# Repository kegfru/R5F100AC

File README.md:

# R5F100AC
Renesas R5F100AC projects

ds18b20 - read from one 1-wire DS18B20 sensor and display temperature on SHD0028 7-segment display (http://www.smartmodule.ru/0028.html, based on SD16739STR)

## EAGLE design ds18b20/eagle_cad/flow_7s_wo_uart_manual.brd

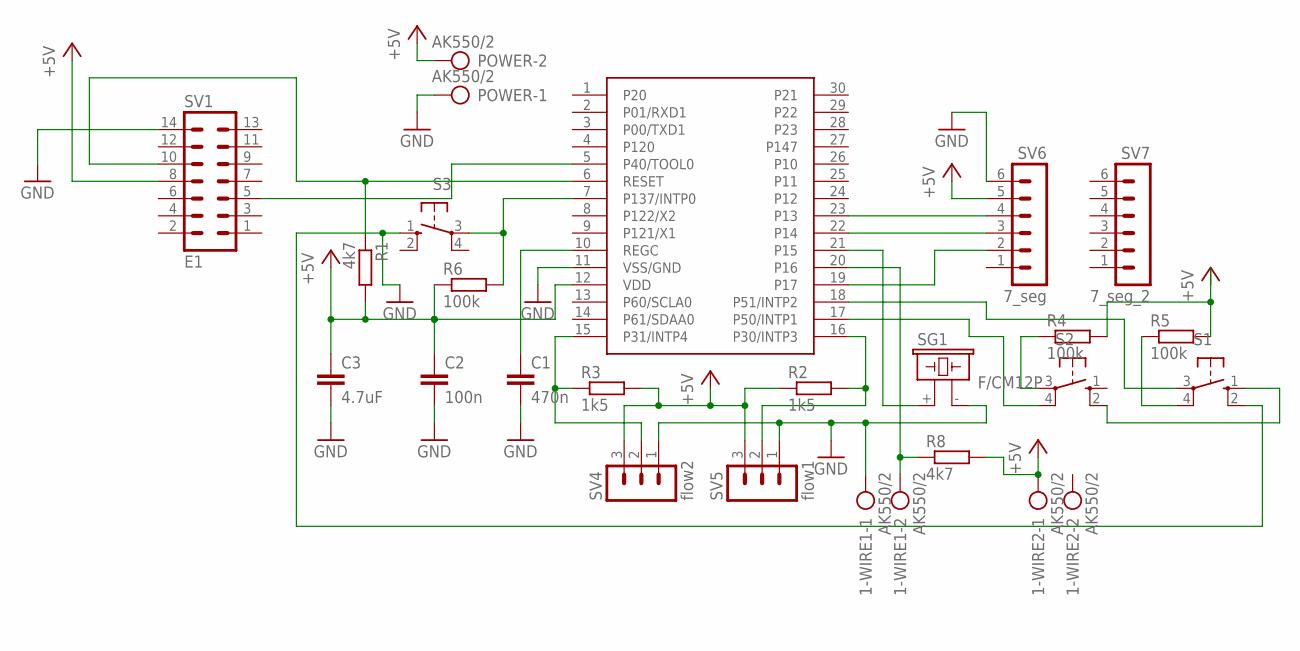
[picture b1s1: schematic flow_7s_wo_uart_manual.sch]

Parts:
1-WIRE1, 1-WIRE2: AK550/2
C1: 470n; C1206
C2: 100n; C1206
C3: 4.7uF; C1206
POWER: AK550/2
R1, R8: 4k7; R1206
R2, R3: 1k5; R1206
R4, R5, R6: 100k; R1206
S1, S2, S3: 10-XX; B3F-10XX
SG1: F/CM12P
SV1: E1; MA07-2
SV4: flow2; MA03-1
SV5: flow1; MA03-1
SV6: 7_seg; MA06-1
SV7: 7_seg_2; MA06-1
U$1: R5F100A; SSOP30

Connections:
+5V: 1-WIRE2.1, C2.1, C3.1, POWER.2, R1.2, R2.1, R3.2, R4.2, R5.2, R6.1, R8.2, SV1.8, SV4.3, SV5.3, SV6.5, U$1.12 (VDD)
GND: 1-WIRE1.1, C1.2, C2.2, C3.2, POWER.1, S1.2 (S1), S3.1 (S), SG1.- (2), SV1.14, SV4.1, SV5.1, SV6.6, U$1.11 (VSS/GND)
unnamed: C1.1, U$1.10 (REGC)
unnamed: R1.1, SV1.10, U$1.6 (RESET)
unnamed: SV1.5, U$1.5 (P40/TOOL0)
unnamed: R6.2, S3.3, U$1.7 (P137/INTP0)
unnamed: R4.1, S2.3
unnamed: SV6.4, U$1.23 (P13)
unnamed: R2.2, SV5.2, U$1.16 (P30/INTP3)
unnamed: SV6.3, U$1.22 (P14)
unnamed: R3.1, SV4.2, U$1.15 (P31/INTP4)
unnamed: SV6.2, U$1.19 (P17)
unnamed: SG1.+ (1), U$1.21 (P15)
unnamed: S1.3, U$1.18 (P51/INTP2)
unnamed: S2.4 (P1), U$1.17 (P50/INTP1)
unnamed: 1-WIRE1.2, R8.1, U$1.20 (P16)
unnamed: S1.1 (S), S2.2 (S1)
unnamed: R5.1, S1.4 (P1)

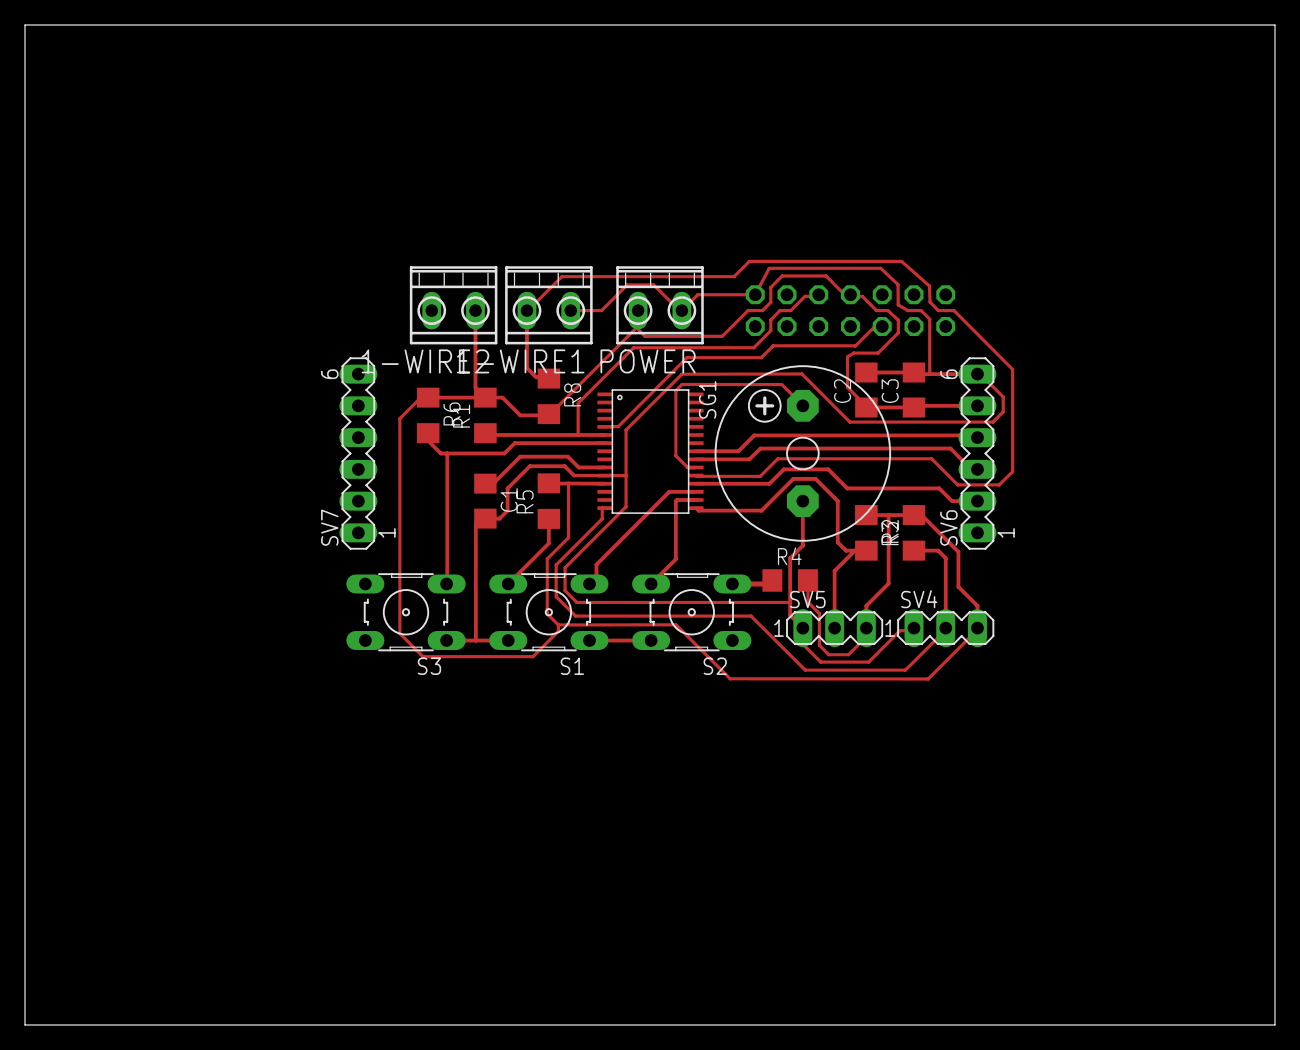
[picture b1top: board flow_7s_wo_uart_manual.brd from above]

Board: 2 copper layers, 100.0 x 80.0 mm, 23 parts (1 on the bottom side), 18 nets.

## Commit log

2017-03-11 initial add
2017-03-11 fix ssled.h
2017-03-11 add ds18b20 description
2017-03-11 Add scheme and pcb in EAGLE CAD
2017-03-11 Clean up main.c
2017-03-11 ds18v20.c to utf-8
2017-03-11 add .gitignore
2017-03-17 formatting
